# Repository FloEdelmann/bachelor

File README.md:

View this project on [CADLAB.io](https://cadlab.io/project/1483). 

# Bachelor's Thesis *Using a Raspberry Pi as a PC-DMX interface*

## Florian Edelmann, November 2017

Official university page: [www.mnm-team.org/pub/Fopras/edel17/](http://www.mnm-team.org/pub/Fopras/edel17/)

**Abstract**

DMX is a common standard in the entertainment technology industry that allows controlling lighting fixtures (like spotlights or strobe lights on a stage) connected over a bus. The DMX source driving the bus is usually a mixing desk console; alternatively, lighting control software on a computer together with a physical PC-DMX interface is often used. The high costs of professional desk consoles and DMX interfaces limits small associations like youth groups to less expensive interfaces that often lack useful features.

This Bachelor's Thesis defines requirements for a PC-DMX interface in this use case, including a price limit and advanced features like the availability of a DMX input port to enable haptic control of software functions. A market study is conducted, which reveals that no existing products match all requirements, so a system design is established, building upon the affordable single-board computer Raspberry Pi. The software basis is provided by *Open Lighting Architecture* (*OLA*), an open-source software that is able to convert different protocols to and from DMX and process the data internally.

OLA is then extended to support DMX output through a USB-DMX adapter by reverse engineering and implementing its protocol. DMX input directly on Raspberry Pi's hardware is possible for the first time through the implementation of SPI bus sampling; other tested approaches were not successful. The validation of the finished PC-DMX interface shows satisfactory fulfillment of the requirements. Future work to improve the system design by making it even less expensive, more easy to use or by adding extra features is possible.

**Full PDF**

see [`edel17.pdf`](edel17.pdf)

### Meta

Written in [Pandoc Markdown](https://pandoc.org/MANUAL.html): [`edel17.md`](edel17.md), [`abstract.md`](abstract.md)

[`Makefile`](Makefile) builds the PDF [`edel17.pdf`](edel17.pdf):

* compile Markdown to LaTeX using Pandoc (with custom filter [`pandoc-filter.js`](pandoc-filter.js))
* replace some strings in the resulting LaTeX code using [`pandoc-postprocessing.js`](pandoc-postprocessing.js)
* run `pdflatex` to create the PDF
* compress it with `gs` (reduces image resolution)

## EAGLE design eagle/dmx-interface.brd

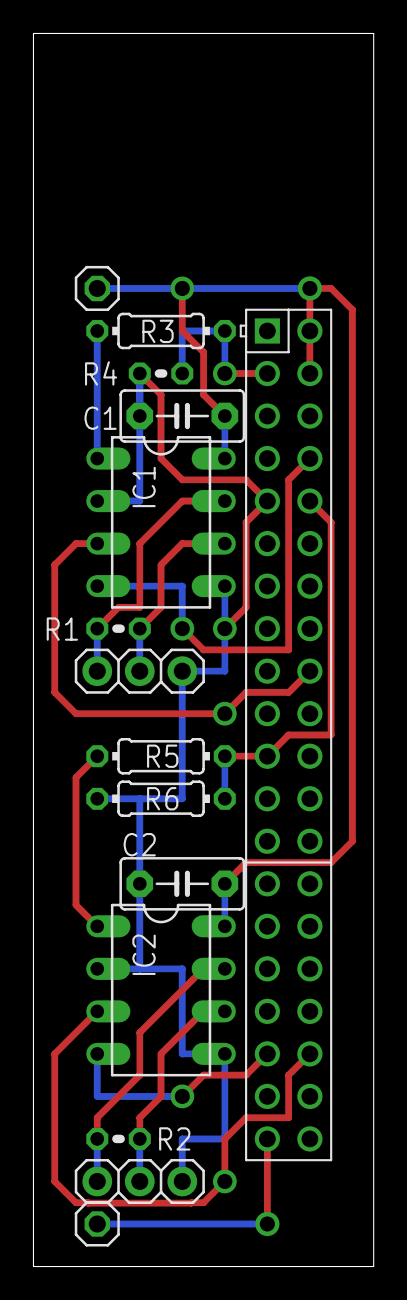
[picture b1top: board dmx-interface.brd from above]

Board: 2 copper layers, 20.3 x 73.7 mm, 15 parts (0 on the bottom side), 15 nets.

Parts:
C1, C2: 100n; C5B3
IC1, IC2: 75176B; DIL08
JP1: DMX OUT; 1X03
JP2: DMX IN; 1X03
JP3: +5V; 1X01
JP4: GND; 1X01
R1, R2: 120; 0204V
R3, R5: 1k; 0204/7
R4: 2k; 0204V
R6: 2k; 0204/7
X1: RASPI_GPIO_B+#_PIN; RASPI_GPIO_B+_PIN

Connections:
+5V: C1.1, C2.1, IC1.8, IC2.8, JP3.1, X1.2, X1.4
GND: C1.2, C2.2, IC1.2, IC1.5, IC2.2, IC2.5, JP1.1, JP2.1, R4.2, R6.1, X1.9
unnamed: IC2.1, R5.2
unnamed: R5.1, R6.2, X1.10, X1.21
unnamed: IC1.6, JP1.2, R1.2
unnamed: R3.1, R4.1, X1.3
unnamed: IC2.4, X1.35
unnamed: IC1.4, X1.8
unnamed: IC1.7, JP1.3, R1.1
unnamed: IC2.7, JP2.3, R2.1
unnamed: IC2.6, JP2.2, R2.2
unnamed: IC2.3, X1.36
unnamed: IC1.3, X1.18
unnamed: JP4.1, X1.39
unnamed: IC1.1, R3.2

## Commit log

2018-03-15 Initial commit
    on GitHub, at least ;)
    The local git history contains some non-public files, though.
2018-11-30 Backlink to CADLAB.io has been added.
